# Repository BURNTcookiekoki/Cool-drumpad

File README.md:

# Cool DrumPad

This design includes 9 panels dedicated for drum samples and 3 buttons to record, loop, and discard your drum samples. To know if you recording a led will light up when pressing record and after you finish just press the record button again and press loop to start looping the record and finally to stop just hit discard.

How to use firmware:
1. Install python
2. Install Arduino
3. pip install PySide6 sounddevice soundfile numpy pyserial
4. pip install PySide6 pygame pyserial
5. Download firmware for arduino and files from github
6. In Arduino IDE, install the Adafruit MPR121 library and install the txt. file from the github
7. just download python into pc
8. cd Desktop python drum_app.py

#Aim

2. make some drum sticks covered in copper take so it touches your skin and also touch the copper drum pads

[BOM.csv](https://github.com/user-attachments/files/33946401/BOM.csv)
"Reference","Qty","Value","DNP","Exclude from BOM","MANUFACTURER","Price","Link"
"U2","1","MPR121QR2","","","Aliexpress","2.27","https://www.aliexpress.com/item/1005013306234663.html?spm=a2g0o.productlist.main.9.78502ce709cZgZ&algo_pvid=d55d0a4b-5fb9-44ea-b6e5-e6405c35060f&algo_exp_id=d55d0a4b-5fb9-44ea-b6e5-e6405c35060f-8&pdp_ext_f=%7B""order""%3A""4""%2C""eval""%3A""1""%2C""fromPage""%3A""search""%7D&pdp_npi=6%40dis%21NZD%2112.09%213.99%21%21%2145.05%2114.87%21%402103138417929876565176883e0fc1%2112000060756763011%21sea%21NZ%216506842476%21X%211%210%21n_tag%3A-29911%3Bd%3Abebf9545%3Bm03_new_user%3A-29895&curPageLogUid=oIzFFsYNV0GG&utparam-url=scene%3Asearch%7Cquery_from%3A%7Cx_object_id%3A1005013306234663%7C_p_origin_prod%3A"
"R1","1","330Ω","","","Aliespress","2.67","https://www.aliexpress.com/item/32315881534.html?spm=a2g0o.productlist.main.1.6e8e413foguZX7&algo_pvid=17d7732f-e1f3-4168-8fb1-1a5db91a6bce&algo_exp_id=17d7732f-e1f3-4168-8fb1-1a5db91a6bce-0&pdp_ext_f=%7B""order""%3A""1001""%2C""eval""%3A""1""%2C""fromPage""%3A""search""%7D&pdp_npi=6%40dis%21NZD%214.69%214.69%21%21%212.62%212.62%21%402101d2e717929875926014633e0e55%2158247725726%21sea%21NZ%216506842476%21X%211%210%21n_tag%3A-29911%3Bd%3Abebf9545%3Bm03_new_user%3A-29895&curPageLogUid=Mmi85OMOpOB3&utparam-url=scene%3Asearch%7Cquery_from%3A%7Cx_object_id%3A32315881534%7C_p_origin_prod%3A"
"D1","1","LED","","","Aliexpress","3.47","https://www.aliexpress.com/item/1005008337998466.html?spm=a2g0o.productlist.main.4.1c7755d1QMiA8U&aem_p4p_detail=202610252103392979921725783640001546625&algo_pvid=df0c1570-28b8-46d1-9f9b-6909eb34c2d2&algo_exp_id=df0c1570-28b8-46d1-9f9b-6909eb34c2d2-3&pdp_ext_f=%7B""order""%3A""362""%2C""eval""%3A""1""%2C""fromPage""%3A""search""%7D&pdp_npi=6%40dis%21NZD%216.29%216.29%21%21%2123.44%2123.44%21%4021030cd817929874191488840e0dc5%2112000046949939825%21sea%21NZ%216506842476%21X%211%210%21n_tag%3A-29911%3Bd%3Abebf9545%3Bm03_new_user%3A-29895&curPageLogUid=PoFXZIvLzD3i&utparam-url=scene%3Asearch%7Cquery_from%3A%7Cx_object_id%3A1005008337998466%7C_p_origin_prod%3A&search_p4p_id=202610252103392979921725783640001546625_1"
"U3","1","Waveshare ESP32-S3-ZERO","","","Aliexpress","9.92","https://www.aliexpress.com/item/1005009800317016.html?spm=a2g0o.productlist.main.1.51405714YcEamr&algo_pvid=6e1843de-b1f4-4d0f-a785-bdeb93b15b41&algo_exp_id=6e1843de-b1f4-4d0f-a785-bdeb93b15b41-0&pdp_ext_f=%7B""order""%3A""161""%2C""eval""%3A""1""%2C""fromPage""%3A""search""%7D&pdp_npi=6%40dis%21NZD%2114.69%2114.69%21%21%2154.73%2154.73%21%402101ca9517929877681285062e0d41%2112000050208860815%21sea%21NZ%216506842476%21X%211%210%21n_tag%3A-29911%3Bd%3Abebf9545%3Bm03_new_user%3A-29895&curPageLogUid=YbawcqN34YQf&utparam-url=scene%3Asearch%7Cquery_from%3A%7Cx_object_id%3A1005009800317016%7C_p_origin_prod%3A"
"J2","1","Breadboard","","","Jaycar","15.34","https://www.jaycar.co.nz/arduino-compatible-breadboard-with-830-tie-points/p/PB8815"

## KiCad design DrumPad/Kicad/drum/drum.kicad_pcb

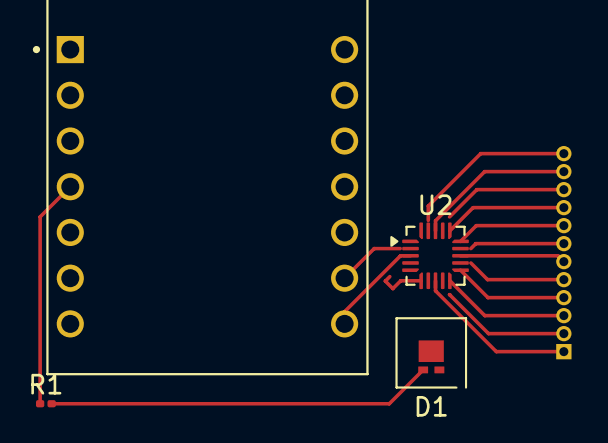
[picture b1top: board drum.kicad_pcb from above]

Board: 2 copper layers, 5 parts (1 on the bottom side), 17 nets.

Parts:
D1: LED; LED-L1T2_LUMILEDS
J1: Copper con; PinHeader_1x12_P1.00mm_Horizontal
R1: 330Ω; R_0201_0603Metric
U2: MPR121QR2; UQFN-20_3x3mm_P0.4mm
U3: Waveshare ESP32-S3-ZERO; XIAO ESP32-S3

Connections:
unnamed: D1.2 (A), R1.2
unnamed: J1.1, U2.8 (ELE0)
unnamed: J1.2, U2.9 (ELE1)
unnamed: J1.3, U2.10 (ELE2)
unnamed: J1.4, U2.11 (ELE3)
unnamed: J1.5, U2.12 (LED0/ELE4)
unnamed: J1.6, U2.13 (LED1/ELE5)
unnamed: J1.7, U2.14 (LED2/ELE6)
unnamed: J1.8, U2.15 (LED3/ELE7)
unnamed: J1.9, U2.16 (LED4/ELE8)
unnamed: J1.10, U2.17 (LED5/ELE9)
unnamed: J1.11, U2.18 (LED6/ELE10)
unnamed: J1.12, U2.19 (LED7/ELE11)
unnamed: U2.4 (ADDR), U2.6 (VSS)
unnamed: U2.2 (SCL), U3.9 (GP9)
unnamed: U2.3 (SDA), U3.8 (GP8)
unnamed: R1.1, U3.4 (GP4)

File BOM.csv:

"Reference","Qty","Value","DNP","Exclude from BOM","MANUFACTURER","Price","Link"
"U2","1","MPR121QR2","","","Aliexpress","2.27","https://www.aliexpress.com/item/1005013306234663.html?spm=a2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""order""%3A""4""%2C""eval""%3A""1""%2C""fromPage""%3A""search""%7D&pdp_npi=6%40dis%21NZD%2112.09%213.99%21%21%2145.05%2114.87%21%402103138417929876565176883e0fc1%2112000060756763011%21sea%21NZ%216506842476%21X%211%210%21n_tag%3A-29911%3Bd%3Abebf9545%3Bm03_new_user%3A-29895&curPageLogUid=oIzFFsYNV0GG&utparam-url=scene%3Asearch%7Cquery_from%3A%7Cx_object_id%3A1005013306234663%7C_p_origin_prod%3A"
"R1","1","330Ω","","","Aliespress","2.67","https://www.aliexpress.com/item/32315881534.html?spm=a2g0o.p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""order""%3A""1001""%2C""eval""%3A""1""%2C""fromPage""%3A""search""%7D&pdp_npi=6%40dis%21NZD%214.69%214.69%21%21%212.62%212.62%21%402101d2e717929875926014633e0e55%2158247725726%21sea%21NZ%216506842476%21X%211%210%21n_tag%3A-29911%3Bd%3Abebf9545%3Bm03_new_user%3A-29895&curPageLogUid=Mmi85OMOpOB3&utparam-url=scene%3Asearch%7Cquery_from%3A%7Cx_object_id%3A32315881534%7C_p_origin_prod%3A"
"D1","1","LED","","","Aliexpress","3.47","https://www.aliexpress.com/item/1005008337998466.html?spm=a2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""order""%3A""362""%2C""eval""%3A""1""%2C""fromPage""%3A""search""%7D&pdp_npi=6%40dis%21NZD%216.29%216.29%21%21%2123.44%2123.44%21%4021030cd817929874191488840e0dc5%2112000046949939825%21sea%21NZ%216506842476%21X%211%210%21n_tag%3A-29911%3Bd%3Abebf9545%3Bm03_new_user%3A-29895&curPageLogUid=PoFXZIvLzD3i&utparam-url=scene%3Asearch%7Cquery_from%3A%7Cx_object_id%3A1005008337998466%7C_p_origin_prod%3A&search_p4p_id=202610252103392979921725783640001546625_1"
"U3","1","Waveshare ESP32-S3-ZERO","","","Aliexpress","9.92","https://www.aliexpress.com/item/1005009800317016.html?spm=a2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""order""%3A""161""%2C""eval""%3A""1""%2C""fromPage""%3A""search""%7D&pdp_npi=6%40dis%21NZD%2114.69%2114.69%21%21%2154.73%2154.73%21%402101ca9517929877681285062e0d41%2112000050208860815%21sea%21NZ%216506842476%21X%211%210%21n_tag%3A-29911%3Bd%3Abebf9545%3Bm03_new_user%3A-29895&curPageLogUid=YbawcqN34YQf&utparam-url=scene%3Asearch%7Cquery_from%3A%7Cx_object_id%3A1005009800317016%7C_p_origin_prod%3A"
"J2","1","Breadboard","","","Jaycar","15.34","https://www.jaycar.co.nz/arduino-compatible-breadboard-with-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"
